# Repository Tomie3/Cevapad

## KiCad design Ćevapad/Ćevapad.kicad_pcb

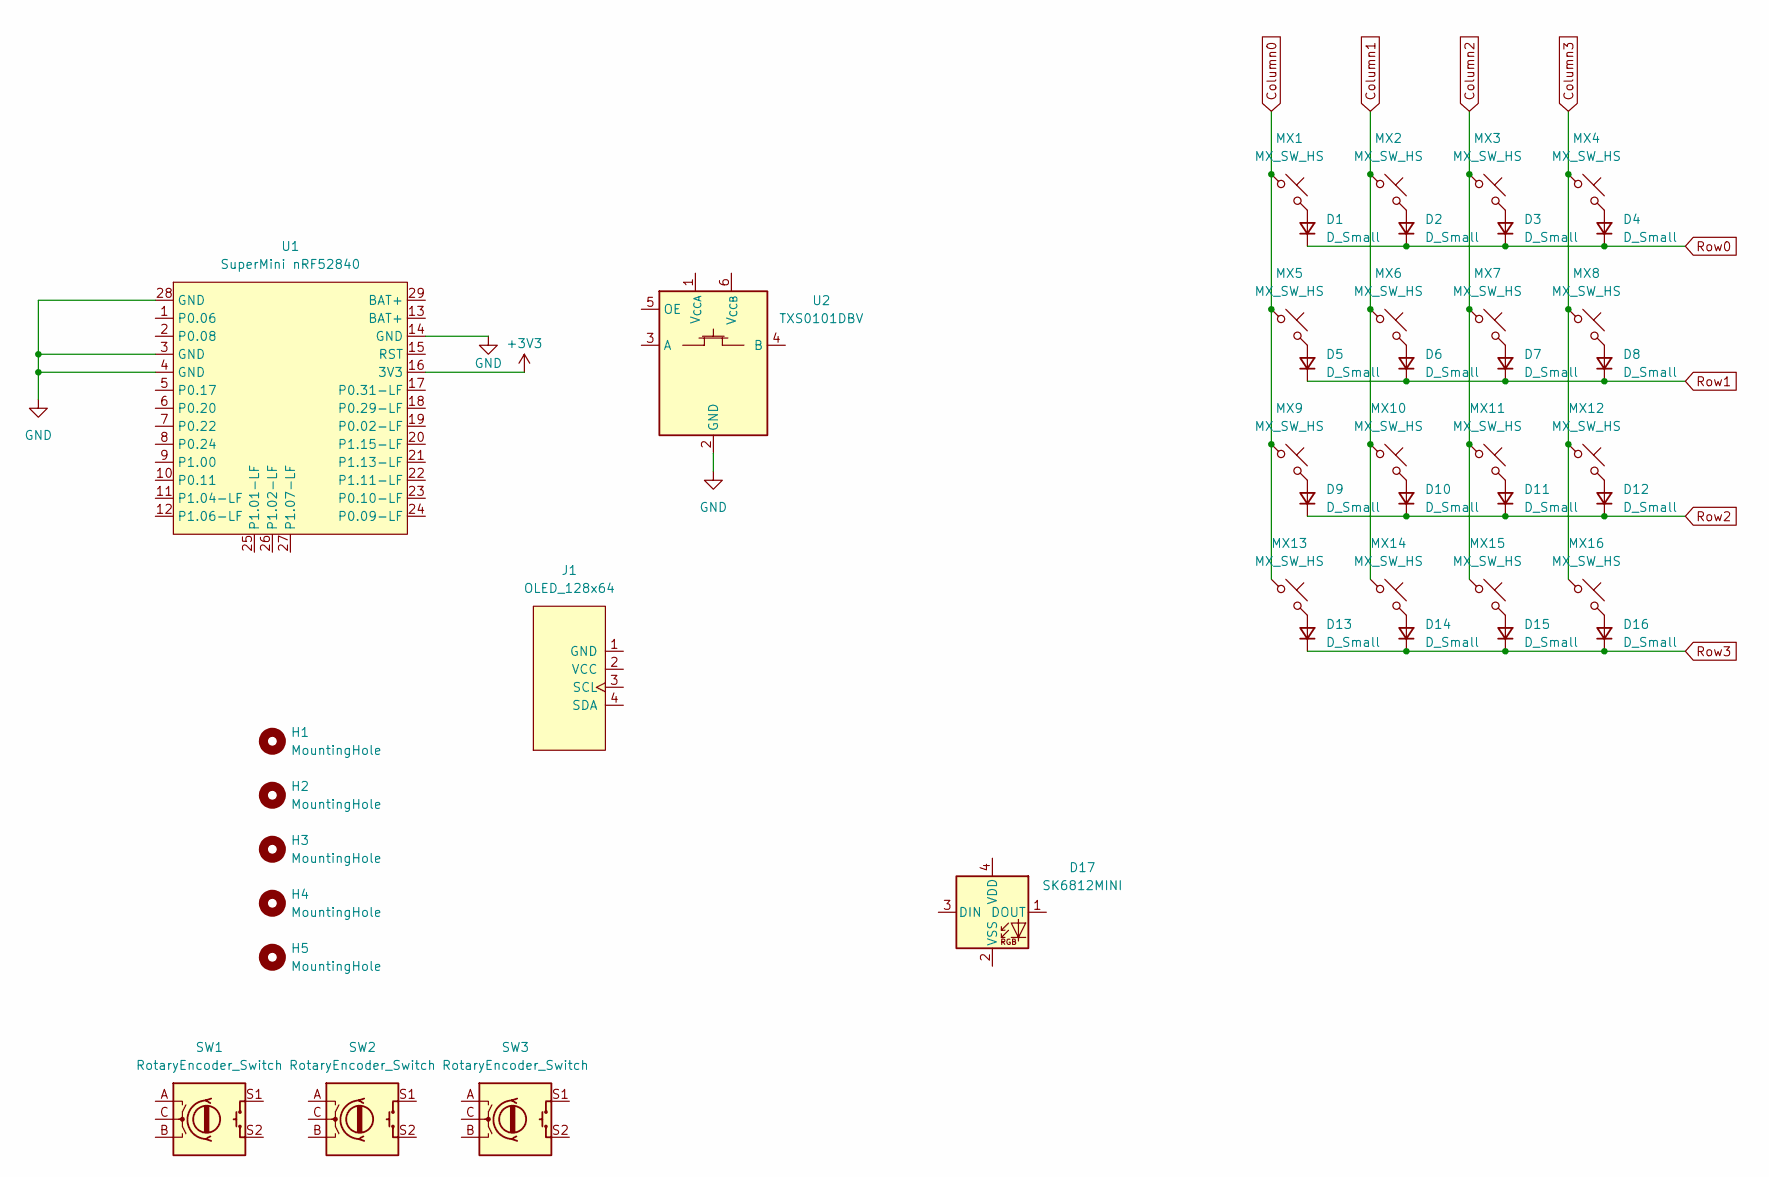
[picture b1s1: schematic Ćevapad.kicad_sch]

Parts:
D1, D2, D3, D4, D5, D6, D7, D8, D9, D10, D11, D12, D13, D14, D15, D16: D_Small; D_0805_2012Metric_Pad1.15x1.40mm_HandSolder
D17: SK6812MINI; LED_SK6812MINI_PLCC4_3.5x3.5mm_P1.75mm
H1, H2, H3, H4, H5: MountingHole; MountingHole_2.2mm_M2_ISO7380_Pad
J1: OLED_128x64
MX1, MX2, MX3, MX4, MX5, MX6, MX7, MX8, MX9, MX10, MX11, MX12, MX13, MX14, MX15, MX16: MX_SW_HS; SW_MX_HS_CPG151101S11_1u
SW1, SW2, SW3: RotaryEncoder_Switch; ROT_Alps_EC11E-Switch
U1: SuperMini nRF52840; SuperMini_nRF52840_AH_USBup
U2: TXS0101DBV; SOT-23-6

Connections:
+3V3: U1.16 (3V3)
Column0: MX1.1, MX5.1, MX9.1, MX13.1
Column1: MX2.1, MX6.1, MX10.1, MX14.1
Column2: MX3.1, MX7.1, MX11.1, MX15.1
Column3: MX4.1, MX8.1, MX12.1, MX16.1
GND: U1.3 (GND), U1.4 (GND), U1.14 (GND), U1.28 (GND), U2.2 (GND)
unnamed: D1.2 (A), MX1.2
unnamed: D2.2 (A), MX2.2
unnamed: D3.2 (A), MX3.2
unnamed: D4.2 (A), MX4.2
unnamed: D5.2 (A), MX5.2
unnamed: D6.2 (A), MX6.2
unnamed: D7.2 (A), MX7.2
unnamed: D8.2 (A), MX8.2
unnamed: D9.2 (A), MX9.2
unnamed: D10.2 (A), MX10.2
unnamed: D11.2 (A), MX11.2
unnamed: D12.2 (A), MX12.2
unnamed: D13.2 (A), MX13.2
unnamed: D14.2 (A), MX14.2
unnamed: D15.2 (A), MX15.2
unnamed: D16.2 (A), MX16.2
Row0: D1.1 (K), D2.1 (K), D3.1 (K), D4.1 (K)
Row1: D5.1 (K), D6.1 (K), D7.1 (K), D8.1 (K)
Row2: D9.1 (K), D10.1 (K), D11.1 (K), D12.1 (K)
Row3: D13.1 (K), D14.1 (K), D15.1 (K), D16.1 (K)

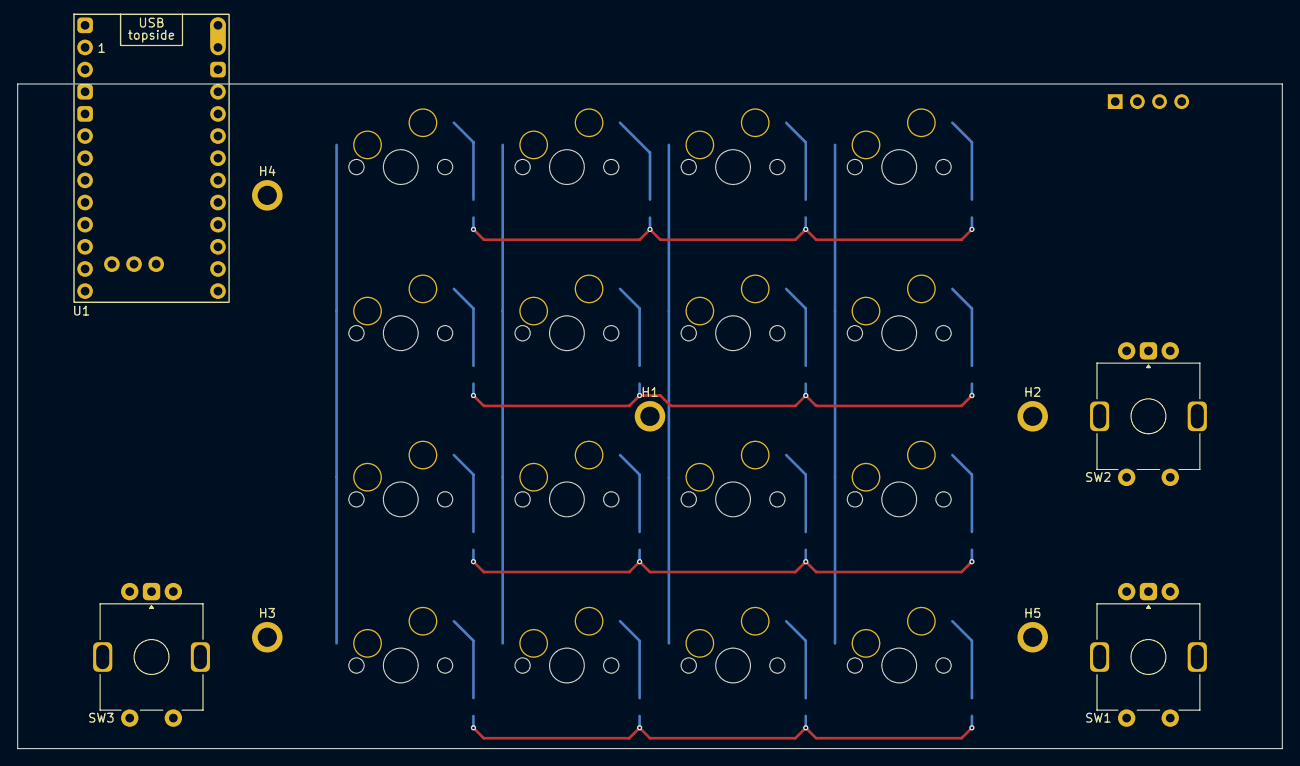
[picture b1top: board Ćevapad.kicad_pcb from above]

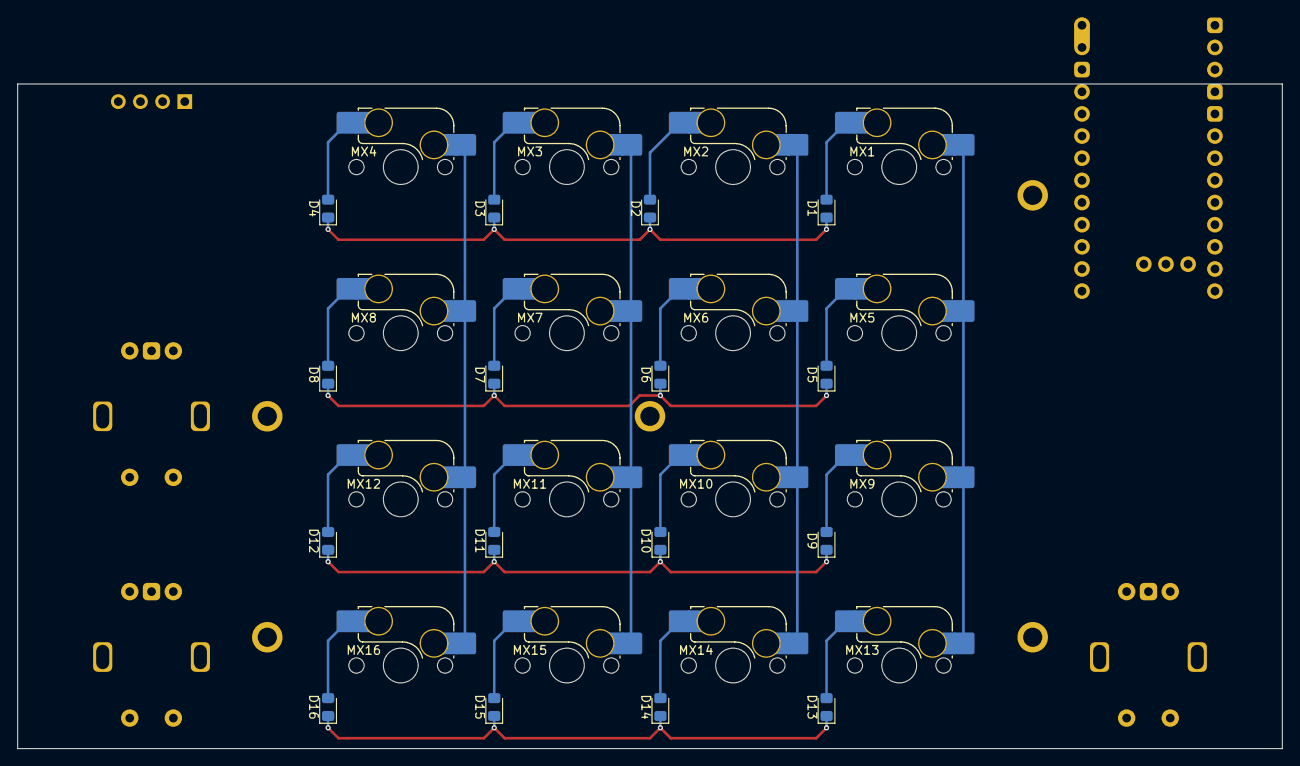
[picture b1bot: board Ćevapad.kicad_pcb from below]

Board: 2 copper layers, 145.0 x 76.2 mm, 42 parts (32 on the bottom side), 25 nets.

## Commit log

2024-11-26 Initalised Project
    Setup Kicad Files and Loaded Libraries
2024-11-26 Kicad Schematics & Roughing Board Layout
